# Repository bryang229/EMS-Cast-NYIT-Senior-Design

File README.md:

# EMS Cast NYIT Senior Design
 
 This Repository will house the Simulation files and modeling data of our project. This will update as needed.

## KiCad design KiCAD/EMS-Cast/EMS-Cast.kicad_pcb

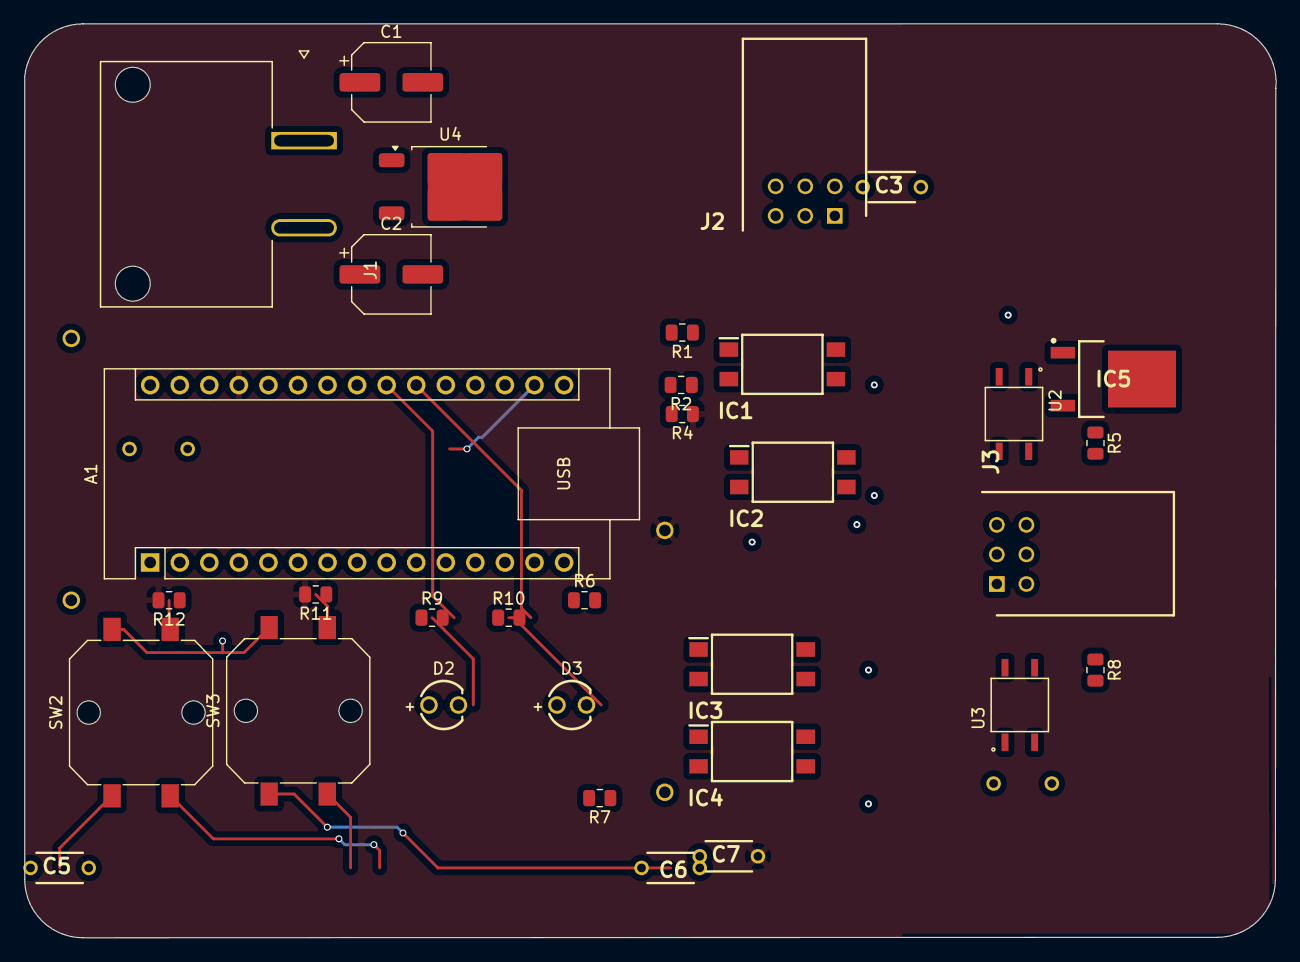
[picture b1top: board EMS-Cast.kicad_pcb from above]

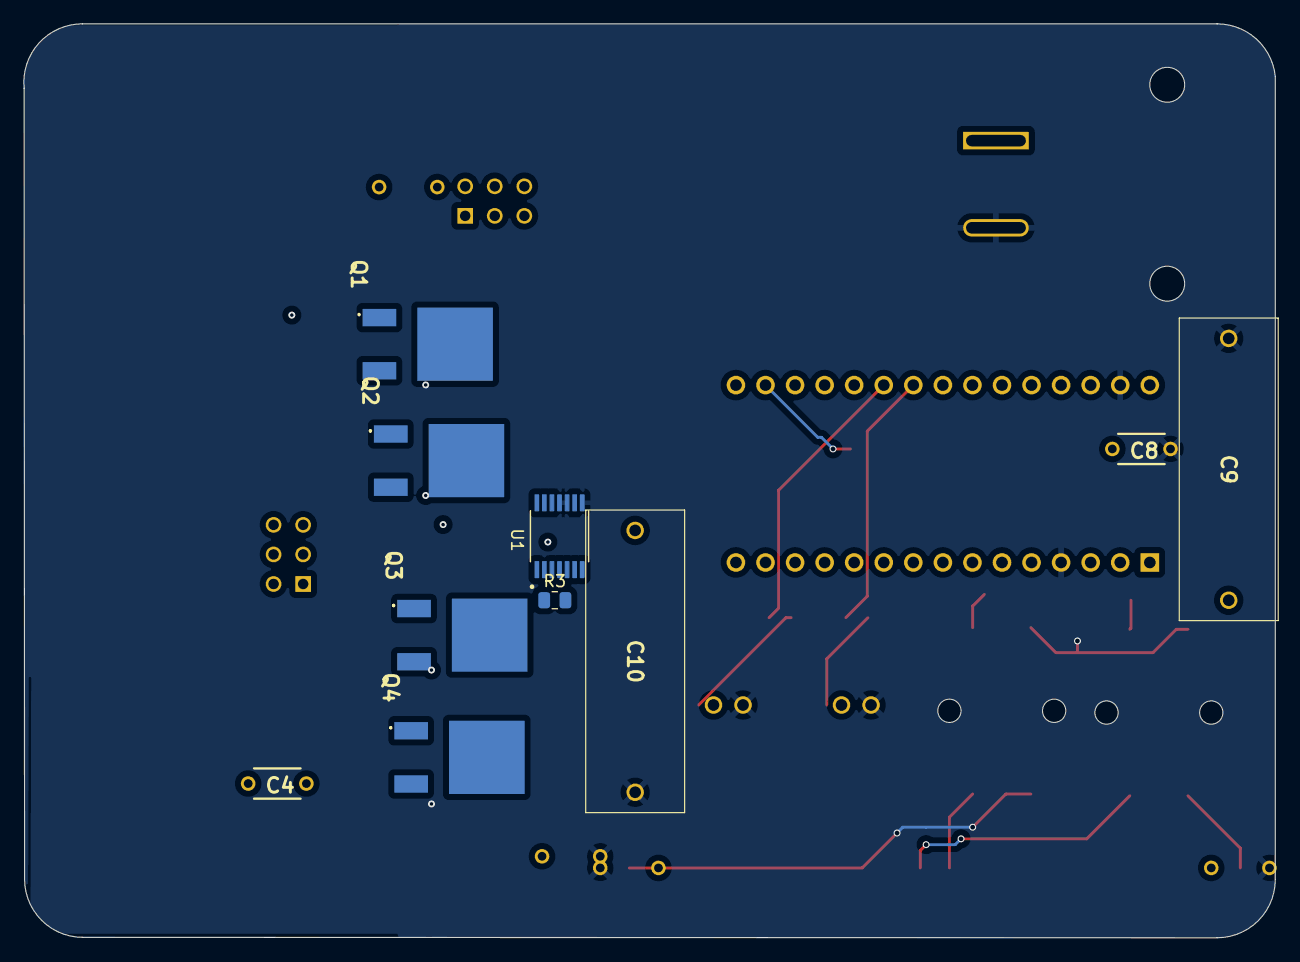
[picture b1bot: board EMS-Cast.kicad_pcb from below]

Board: 2 copper layers, 107.5 x 78.5 mm, 43 parts (10 on the bottom side), 37 nets.

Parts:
A1: Arduino_Nano_v3.x; Arduino_Nano
C1, C2: .01u; CP_Elec_6.3x3
C3, C4, C5, C6, C7, C8: 100n; K104K15X7RF53H5
C9, C10: 1u; ECQE4105KF
D2, D3: LED; WL-TMRC_3MM
IC1, IC2, IC3, IC4: LH1546ADF; SOP254P980X425-4N
IC5: KF33BDT-TR; TO228P972X240-3N
J1: 1720430202; MOLEX_1720430202
J2, J3: 5-103166-1
Q1, Q2, Q3, Q4: STD25NF20
R1, R2, R6, R7: 220; R_0805_2012Metric
R3, R4, R9, R10: 1K; R_0805_2012Metric
R5, R8: 1.5M; R_0805_2012Metric
R11, R12: 1k; R_0805_2012Metric
SW2, SW3: SW_Push; SW_Push_1P1T_NO_CK_PTS125Sx43PSMTR
U1: AD5252BRUZ10-RL7; SOP65P640X120-14N
U2, U3: VOM1271T; SOIC254P695X242-4N
U4: KF80BDT; TO-252-2

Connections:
+3.3V: A1.17 (3V3), C8.2, C9.1
+5V: A1.27 (+5V), C7.2, C10.1, R3.1, R4.1, R11.2, R12.2, U1.1 (VDD), U1.3 (WP*)
/CH1N_IN: IC2.4 (S1), J2.2, Q2.3 (S)
/CH1N_OUT: IC2.3 (S2), J3.2
/CH1P_IN: IC1.3 (S2), J2.1, Q1.3 (S)
/CH1P_OUT: IC1.4 (S1), J3.1
/CH1_EN_1: A1.7 (D4), R1.2
/CH1_EN_2: A1.8 (D5), R2.2
/CH2N_IN: IC4.4 (S1), J2.6, Q4.3 (S)
/CH2N_OUT: IC4.3 (S2), J3.6
/CH2P_IN: IC3.3 (S2), J2.5, Q3.3 (S)
/CH2P_OUT: IC3.4 (S1), J3.5
/CH2_EN_1: A1.9 (D6), R6.2
/CH2_EN_2: A1.10 (D7), R7.2
/SCLK: A1.24 (A5), U1.9 (SCL)
/SDA: A1.23 (A4), U1.7 (SDA)
/SW_CH1: A1.11 (D8), C6.2, R12.1, SW2.2
/SW_CH2: A1.12 (D9), C5.2, R11.1, SW3.2
/V_REF1: U1.4 (W1), U2.1
/V_REF2: U1.14 (W3), U3.1
GND: A1.4 (GND), A1.29 (GND), C1.2, C2.2, C5.1, C6.1, C7.1, C8.1, C9.2, C10.2, D2.1 (K), D3.1 (K), IC1.2 (C), IC2.2 (C), IC3.2 (C), IC4.2 (C), IC5.4 (GND_TAB), J1.2, SW2.1, SW3.1, U1.2 (AD0), U1.8 (VSS), U1.10 (DGND), U1.11 (AD1), U2.2, U3.2, U4.2 (GND)
unnamed: A1.21 (A2), R10.2
unnamed: A1.22 (A3), R9.2
unnamed: A1.30 (VIN), C2.1, IC5.3 (OUTPUT), U4.3 (VO)
unnamed: D2.2 (A), R9.1
unnamed: D3.2 (A), R10.1
unnamed: IC1.1 (A), R1.1
unnamed: IC2.1 (A), R2.1
unnamed: IC3.1 (A), R6.1
unnamed: IC4.1 (A), R7.1
unnamed: C1.1, IC5.1 (INPUT), J1.1
unnamed: C3.2, Q1.2 (D), Q2.2 (D), R5.2, U2.3
unnamed: C3.1, Q1.1 (G), Q2.1 (G), R5.1, U2.4
unnamed: C4.2, Q3.2 (D), Q4.2 (D), R8.2, U3.3
unnamed: C4.1, Q3.1 (G), Q4.1 (G), R8.1, U3.4
unnamed: R3.2, U1.6 (A1)
unnamed: R4.2, U1.12 (A3)

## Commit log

2024-11-11 Base upload
2024-11-12 Added KiCAD
    Added Schematic based on https://github.com/PedroLopes/openEMSstim and started PCB tracing for reference only
2025-02-03 Multiple Changes
    - Updated KICAD for proposal images
    - Added Arduino code folder with basic .ino code (basic requirement and temporary pin mappings)
